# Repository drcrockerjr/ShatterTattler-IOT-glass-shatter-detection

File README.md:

# ShatterTattler

ShatterTattler is an embedded audio signal analysis platform designed to run deep learning sound event classification in a more decentralized manner. The system is specifically built for low power, glass shatter event detection in residential or commercial environments. Due to the flexible deep learning approach the system can be trained and optimized for real time acoustic sensing applications such as environmental monitoring, industrial condition assessment, and anomaly detection.

# Overview

ShatterTattler integrates high-fidelity audio capture with efficient preprocessing and inference. It leverages the ESP32-S3 microcontroller for connectivity and control, with a PCM1841-Q1 quad channel ADC for microphone audio input from multiple sources. Audio Telemetry data is then transported vio BLE 5.0 from the edge ESP32 to an Nvidia Jetson Orin Nano where the bulk of the heavy processing occurs. Upon data arrival, preprocessing (filtering, spectral analysis, feature extraction) is performed on the Jetson upon data arrival device CPU before LSTM model inference occurs on the device GPU. A general overview is described in this image: 

# Hardware Components
## ESP32-S3

- Integrated Wi-Fi + Bluetooth LE 5.0
- Up to 512KB SRAM and external PSRAM support
- PCM1841-Q1 (TI Burr-Brown™ Audio ADC) Quad-channel, 32-bit, up to 192kHz sampling
- 123dB dynamic range (with DRE enabled)
- Interfaces: TDM, I²S, or Left-Justified formats
- Integrated MICBIAS (2.75V, 20mA drive) for powering microphones
- Built-in PLL, DC-removal HPF, and configurable digital filters
- Low power consumption (~18–25mW/channel at 48kHz)

## Software Stack

- Arduino Framework (ESP-IDF optional): for ESP32-S3 development
- BLE GATT Server: for wireless configuration and streaming metadata
- DSP Preprocessing: band-pass, low-pass, amplification
- ML Inference: models trained in PyTorch/TensorFlow Jetson runs model directly

# Key Features

- Multi channel audio capture and preprocessing at the edge
- Jeston device neural network inference (CNN, LSTM, or Transformer-lite models)
- BLE-based telemetry and configuration
- Modular design for integration into larger IoT sensing systems

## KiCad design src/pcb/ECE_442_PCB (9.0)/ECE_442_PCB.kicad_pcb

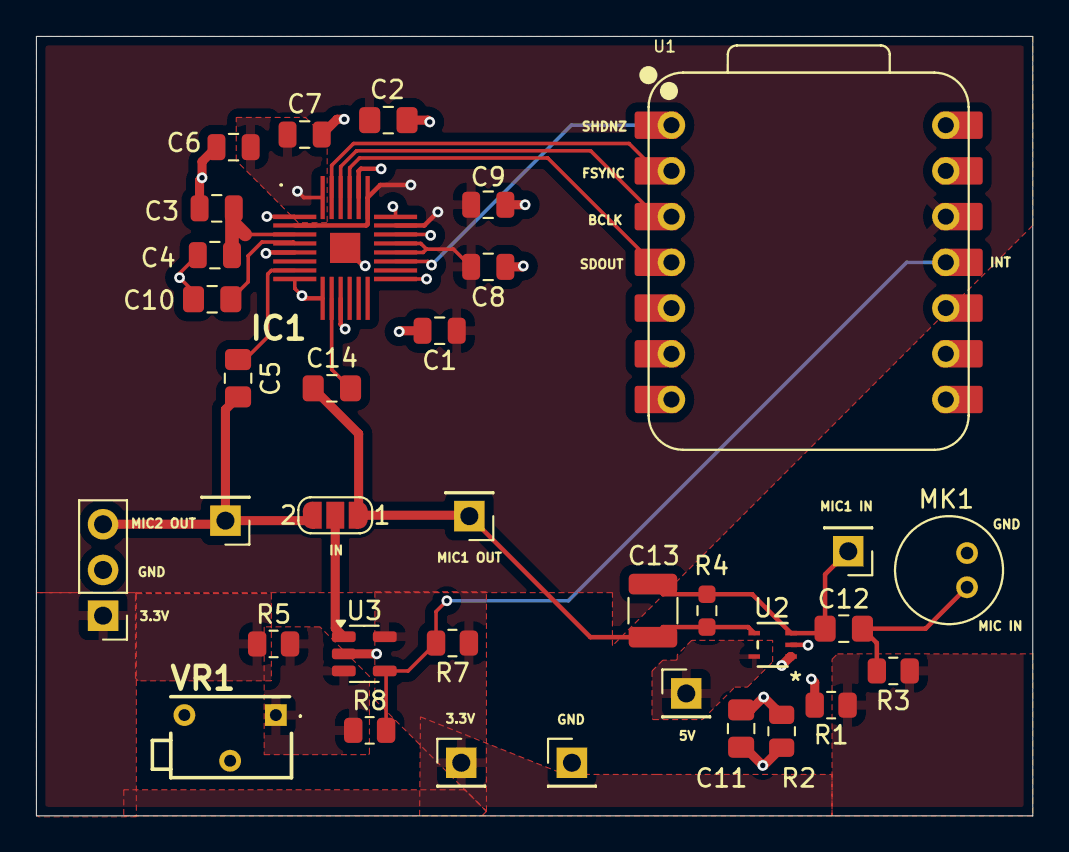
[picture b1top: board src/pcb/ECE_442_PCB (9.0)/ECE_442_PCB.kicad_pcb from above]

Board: 2 copper layers, 55.4 x 43.3 mm, 35 parts (0 on the bottom side), 20 nets.

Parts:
C1, C3, C6, C9: 0.1uF; C_0805_2012Metric
C2, C5, C10, C14: 1uF; C_0805_2012Metric_Pad1.18x1.45mm_HandSolder
C4, C7, C8: 10uF; C_0805_2012Metric
C11: 3.3u; C_0805_2012Metric_Pad1.18x1.45mm_HandSolder
C12: 4.7u; C_0805_2012Metric_Pad1.18x1.45mm_HandSolder
C13: 17.6u; C_1210_3225Metric
IC1: PCM1841QRGERQ1
J1, J2, J3, J4, J5, J7: Conn_01x01_Pin; PinHeader_1x01_P2.54mm_Vertical
J6: Conn_01x03_Pin; PinHeader_1x03_P2.54mm_Vertical
JP2: SolderJumper_3_Open; SolderJumper-3_P1.3mm_Open_RoundedPad1.0x1.5mm_NumberLabels
MK1: Microphone; CUI_CMC-5042PF-AC
R1, R2, R5, R8: 100K; R_0805_2012Metric
R3: 5.9K; R_0805_2012Metric
R4: 67.8K; R_0603_1608Metric_Pad0.98x0.95mm_HandSolder
R7: 10K; R_0805_2012Metric
U1: MOUDLE-SEEEDUINO-XIAO-ESP32S3; XIAO-ESP32S3-DIP
U2: TLV6741DCKR; DCK5_TEX-L
U3: TL331KDBVR; SOT-23-5
VR1: 3266X-1-104LF; 3266X1104LF

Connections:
+3.3V: C1.2, C2.2, C8.2, C9.2, IC1.1 (AVDD), IC1.15 (FMT1), IC1.16 (FMT0), IC1.18 (MD0), IC1.19 (IOVDD), J3.1, J6.1, R1.1, R3.1, R5.1, R7.1, U1.12 (3V3), U3.5 (V+)
+5V: J5.1, U2.5 (V+)
/AREG: C3.1, C4.1, IC1.2 (AREG)
/DREG: C6.1, C7.2, IC1.24 (DREG)
/IN+: C11.2, R1.2, R2.1, U2.1 (+IN)
/MIC: C12.1, MK1.MIC, R3.2
BCLK: IC1.22 (BCLK), U1.3 (PA10_A2_D2)
FSYNC: IC1.23 (FSYNC), U1.2 (PA4_A1_D1)
GND: C1.1, C2.1, C3.2, C4.2, C6.2, C7.1, C8.1, C9.1, C10.1, C11.1, IC1.4 (AVSS_1), IC1.7 (IN1M), IC1.9 (IN2M), IC1.17 (MSZ), IC1.20 (MD1), IC1.25 (GND), IC1.A1 (AVSS_2), IC1.A2 (AVSS_3), IC1.A3 (AVSS_4), IC1.A4 (AVSS_5), J4.1, J6.2, MK1.GND, R2.2, U1.13 (GND), U2.2 (V), U3.2 (V-), VR1.2 (WIPER)
IN: JP2.2 (C), U3.1 (-)
INT: R7.2, R8.2, U1.11 (PA6_A10_D10_MOSI), U3.4
MIC1_OUT: C13.1, C14.1, J1.1, JP2.1 (A), R4.2, U2.4 (OUT)
MIC2_OUT: C5.1, J6.3, J7.1, JP2.3 (B)
MIC_IN: C12.2, C13.2, J2.1, R4.1, U2.3 (IN)
unnamed: C5.2, IC1.6 (IN1P)
unnamed: C14.2, IC1.8 (IN2P)
unnamed: C10.2, IC1.3 (VREF)
SDOUT: IC1.21 (SDOUT), U1.4 (PA11_A3_D3)
SHDNZ: IC1.14 (SHDNZ), U1.1 (PA02_A0_D0)
VA: R5.2, R8.1, U3.3 (+), VR1.1 (CCW)

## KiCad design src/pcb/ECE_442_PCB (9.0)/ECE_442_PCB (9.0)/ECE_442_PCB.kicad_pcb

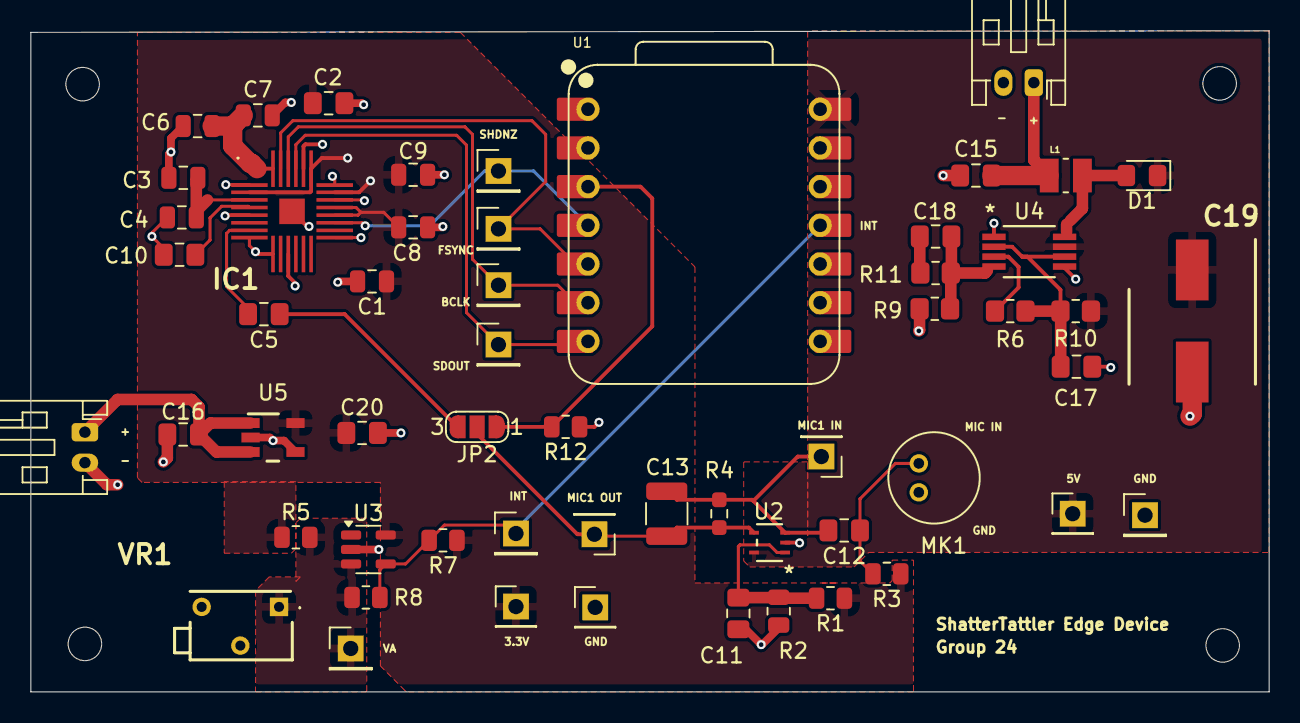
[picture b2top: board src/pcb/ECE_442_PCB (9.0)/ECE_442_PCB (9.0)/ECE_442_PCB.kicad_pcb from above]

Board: 2 copper layers, 81.3 x 43.4 mm, 60 parts (0 on the bottom side), 26 nets.

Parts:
C1, C3, C6, C9: 0.1uF; C_0805_2012Metric
C2, C5, C10: 1uF; C_0805_2012Metric_Pad1.18x1.45mm_HandSolder
C4, C7, C8: 10uF; C_0805_2012Metric
C11: 3.3u; C_0805_2012Metric_Pad1.18x1.45mm_HandSolder
C12: 10uF; C_0805_2012Metric_Pad1.18x1.45mm_HandSolder
C13: 20pF; C_1210_3225Metric
C15: 22 uF; C_0805_2012Metric_Pad1.18x1.45mm_HandSolder
C16, C17, C20: 1 uF; C_0805_2012Metric_Pad1.18x1.45mm_HandSolder
C18: 39 pF; C_0805_2012Metric_Pad1.18x1.45mm_HandSolder
C19: 68 uF; CAPAE830X1050N
D1: D_Schottky; D_0805_2012Metric_Pad1.15x1.40mm_HandSolder
H1, H2, H3, H4: MountingHole; MountingHole_2.2mm_M2
IC1: PCM1841QRGERQ1
J1, J2, J3, J4, J5, J6, J7, J10, J11, J12, J13, J14: Conn_01x01_Pin; PinHeader_1x01_P2.54mm_Vertical
J8, J9: Conn_01x02_Pin; JST_PH_S2B-PH-K_1x02_P2.00mm_Horizontal
JP2: SolderJumper_3_Open; SolderJumper-3_P1.3mm_Open_RoundedPad1.0x1.5mm_NumberLabels
L1: 6.8 uH; INDC2520X120N
MK1: Microphone; CUI_CMC-5042PF-AC
R1, R2, R5, R8: 100K; R_0805_2012Metric
R3: 5.9K; R_0805_2012Metric
R4: 55K; R_0603_1608Metric_Pad0.98x0.95mm_HandSolder
R6: 200 kOhm; R_0805_2012Metric_Pad1.20x1.40mm_HandSolder
R7: 10K; R_0805_2012Metric
R9: 50 kOhm; R_0805_2012Metric_Pad1.20x1.40mm_HandSolder
R10: 49.9 Ohm; R_0805_2012Metric_Pad1.20x1.40mm_HandSolder
R11: 150 kOhm; R_0805_2012Metric_Pad1.20x1.40mm_HandSolder
R12: 3.9K; R_0805_2012Metric
U1: MOUDLE-SEEEDUINO-XIAO-ESP32S3; XIAO-ESP32S3-DIP
U2: TLV6741DCKR; DCK5_TEX-L
U3: TL331KDBVR; SOT-23-5
U4: LMR61428XMM/NOPB; DGK8_TEX-M
U5: TLV73333PQDBVRQ1; DBV0005A_M
VR1: 3266X-1-104LF; 3266X1104LF

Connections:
/AREG: C3.1, C4.1, IC1.2 (AREG)
/DREG: C6.1, C7.2, IC1.24 (DREG)
/IN+: C11.2, R1.2, R2.1, U2.1 (+IN)
/MIC: C12.1, MK1.OUT, R3.2
BCLK: IC1.22 (BCLK), J12.1, U1.6 (PA9_A5_D5_SCL)
FSYNC: IC1.23 (FSYNC), J11.1, U1.5 (PA8_A4_D4_SDA)
GND: C1.1, C2.1, C3.2, C4.2, C6.2, C7.1, C8.1, C9.1, C10.1, C11.1, C15.2, C16.2, C17.2, C19.2 (-), C20.2, IC1.4 (AVSS_1), IC1.7 (IN1M), IC1.9 (IN2M), IC1.17 (MSZ), IC1.20 (MD1), IC1.25 (GND), IC1.A1 (AVSS_2), IC1.A2 (AVSS_3), IC1.A3 (AVSS_4), IC1.A4 (AVSS_5), J4.1, J8.2, J9.2, J14.1, MK1.GND, R2.2, R9.2, R12.1, U1.13 (GND), U2.2 (V), U3.2 (V-), U4.1 (PGND), U4.5 (SGND), U5.2 (GND), U5.4 (NC), VR1.2 (WIPER)
INT: J6.1, R7.2, R8.2, U1.11 (PA6_A10_D10_MOSI), U3.4
MIC1_OUT: C13.1, J1.1, JP2.2 (C), R4.2, U2.4 (OUT)
MIC_IN: C12.2, C13.2, J2.1, R4.1, U2.3 (IN)
unnamed: C18.2, R11.2
unnamed: D1.2 (A), L1.2, U4.8 (SW)
unnamed: C5.2, IC1.6 (IN1P)
unnamed: C10.2, IC1.3 (VREF)
unnamed: C15.1, J8.1, L1.1
unnamed: C16.1, J9.1, U5.1 (IN), U5.3 (EN)
unnamed: C17.1, R6.2, R10.2, U4.2 (EN), U4.6 (VDD)
unnamed: C18.1, R9.1, R11.1, U4.4 (FB)
unnamed: R6.1, U4.3 (FREQ)
OUT1: JP2.1 (A), R12.2, U1.3 (PA10_A2_D2)
OUT2: C5.1, JP2.3 (B)
PS_3.3V: C1.2, C2.2, C8.2, C9.2, C20.1, IC1.1 (AVDD), IC1.15 (FMT1), IC1.16 (FMT0), IC1.18 (MD0), IC1.19 (IOVDD), J3.1, R1.1, R3.1, R5.1, R7.1, U3.5 (V+), U5.5 (OUT)
PS_5V_0.5A: C19.1 (+), D1.1 (K), J5.1, R10.1, U1.14 (5V), U2.5 (V+), U4.7 (BOOT)
SDOUT: IC1.21 (SDOUT), J13.1, U1.7 (PB08_A6_TX)
SHDNZ: IC1.14 (SHDNZ), J10.1, U1.4 (PA11_A3_D3)
VA: J7.1, R5.2, R8.1, U3.3 (+), VR1.1 (CCW)

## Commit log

2024-12-04 start of sound parsing script
2024-12-24 f64 to f16 wave file coe works, event segments now produced
2024-12-26 training/validation works on preprocessed dataset
2025-01-04 training in 16kHz now works, more test scripts created
2025-01-05 start to hub class definition
2025-01-06 hub class progress
2025-01-07 hub progress
2025-01-20 started Ble code
2025-01-22 bluetooth works with esp32, able to connect and recv data
2025-01-23 small ble changes
2025-01-23 small change
2025-01-23 small ble fixes and changes
2025-01-24 big changes to test ble with jetson device and saving arrays to dataset for each edge node
2025-01-24 small ble change
2025-01-30 hub ble changes that need to be merged to main
2025-02-07 checkoff changes
2025-02-20 checkoff stuff added and notification works for email
2025-02-21 small hub change
2025-03-25 deleted pcb files
2025-03-25 updated pcb files
2025-04-22 updated hub code
2025-04-22 changes to hub code
2025-04-22 added heartbeat
2025-04-22 added peripheral file for LED/Speaker functionality
2025-04-25 attempt 2
2025-04-25 attempt 3
2025-05-06 try this
2025-05-10 added alarm edge device
2025-05-10 Waveform saved to proper torch data structure, mel and mfcc generate, need to handle classification, make sure to change nu audio packets back to regular
2025-05-11 saved preliminary model and requirement changes
2025-05-12 adding trained madel
2025-05-12 New logic code for running hub with classes for nodes and better connection management.
2025-05-12 Changed logging level to info
2025-05-12 small fixes to edge node packet management and added more log statements
2025-05-12 Added more logging statements
2025-05-12 import change
2025-05-12 logging statements to verify notify is working
2025-05-12 changed logging level
2025-05-12 logic fix
2025-05-12 logging statements
2025-05-12 edge_node uuid check now isnt case specific
2025-05-12 fixed variable declaration error
2025-05-12 logging added, queue now gets sender uuid
2025-05-12 small changes
2025-05-12 fixed error with predictor
2025-05-12 prediction fix, changed to single feature prediction at a time
2025-05-12 working BLE alarm edge device
2025-05-12 Classification works with trained model, still need to handle filtering of noise spikes
2025-05-13 added functionality for alarm devices
2025-05-13 Alarm works now, still need to figure out notify issues and look for delays that arent needed
2025-05-13 improved client buffer management
2025-05-13 small predictor fix
2025-05-13 client connection logic changes
2025-05-13 client is connected routine fix
2025-05-13 added log statements to wav to feature
2025-05-13 added edge node code and started periodic report implementation
2025-05-13 added recconnect on disconnection
2025-05-13 added reconnection after disconnect
2025-05-13 trying filtering
2025-05-13 debug for filter
2025-05-13 debug 2 for filtering
2025-05-14 added filtering to recv audio signal on hub before classify
2025-05-14 fixed bug causing only one classify, need to delete debug print statments
2025-05-14 added periodic reports
2025-05-14 decreased periodic report interval
2025-05-14 notification debug1
2025-05-14 debug periodic report 2
2025-05-14 debug battery status
2025-05-14 debug for battery
2025-05-14 implemented working periodic report as of 5/14
2025-05-19 added comments to code and auto formatted
